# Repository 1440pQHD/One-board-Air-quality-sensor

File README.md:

# BreatheEasy - One-board-Air-quality-sensor
A simple, cheap-to-build PCB that actively monitors air quality and prevents invisible hazards. It makes protection from environmental hazards accessible to everyone.

The brains of the project are the ESP32 C3-Wroom-02

<b> Why did I choose this board? </b>

Because it includes: Wifi, Bluetooth, more than enough GPIO to last me days, and most importantly,
It's dirt cheap

List of sensors used:
BME280 (Temp & Humidity)
<br> MQ-135 (Hazardous Gas)

<p>
  Powering everything is as simple as plugging in a USB-C cable, something we should all have by now.
</p>
<p>
  The information can be read from a website that the microcontroller hosts on the local network that it's connected to.
</p>

The complete parts list includes:
1. ESP32 C3 Wroom O2
2. MQ-135 GAS sensor (Specifically the one with the digital out pin)
3. BMP280 (We love Bosh)
4. 1x 20k Ohm resistors
5. 3x 10K Ohm resistors
6. 1x 5.1KOhm resistor
7. Sparkfun USB-C Breakout module (6-pin)
8. 2x 6mm Push buttons
9. LD1117
    
The total parts list comes to about 15 euros, which is fairly cheap.
Right now, only the hardware side has been really figured out; the software side is still in early development.

The final PCB design has already been made available for anyone who wants to take a look and/or assemble the PCB.

<h1> The second iteration of the website has been released!</h1>

The second iteration of the website includes:
1. The current humidity.
2. The current temperature.
3. The current alcohol levels (this prototype uses an MQ-3 instead of an MQ-135)
4. The latest event (High temperature, Low temperature, high alcohol, etc.)
5. Uptime and time since last update.
6. An alarm played through the browser.
7. **Sub-pages for every single metric.**
8. **Live gradient for the background.**
9. **System statistics including: Available RAM and WIFI signal strength**
10. **Min/Max Values for every sensor**

<h2> How does it work? </h2>

The ESP32 reads the MQ-135 and DHT11 values through a voltage divider, since the sensor outputs up to 5v but the ESP32 can handle only 3.3V, and sends them in a JSON string to the browser you're viewing the website from.

The neat part is that, since the browser does all the heavy lifting, the ESP32 doesn't use much computing power.

The entire website structure is uploaded via a plugin called "LittleFS". It gives the ability to upload multiple files to the ESP32 to achieve an organized file structure, instead of having everything in one HTML file.

The website's modern look is achieved through fairly simple CSS.

<h2> I'm hoping by the end of the week I'll have gotten all the parts to build the final device. </h2>

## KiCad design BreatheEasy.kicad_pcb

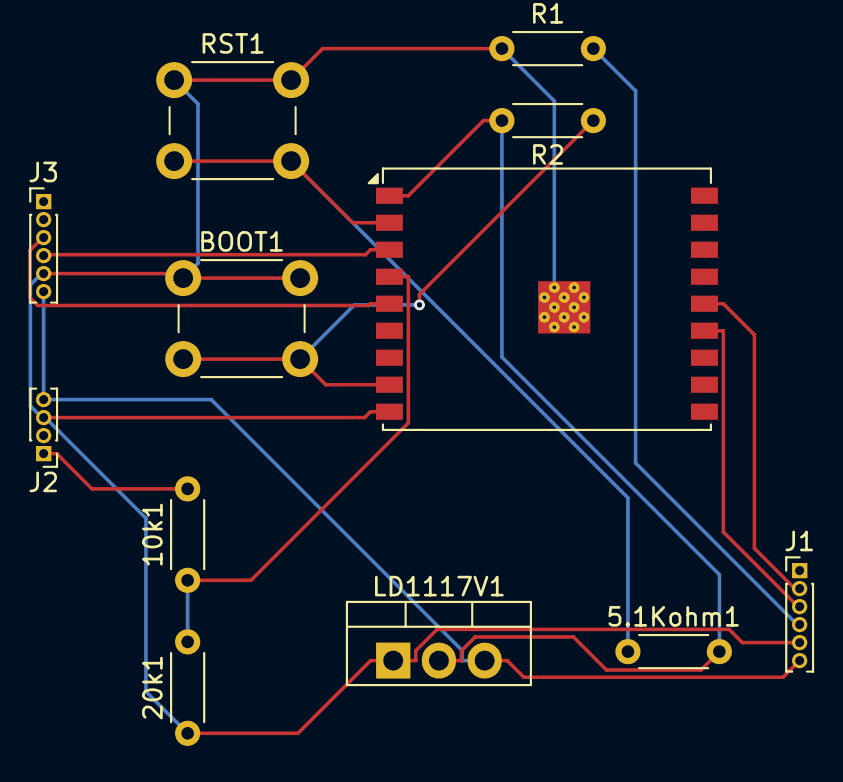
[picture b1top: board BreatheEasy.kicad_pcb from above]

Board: 2 copper layers, 12 parts (0 on the bottom side), 12 nets.

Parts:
5.1Kohm1, 10k1, 20k1: R; R_Axial_DIN0204_L3.6mm_D1.6mm_P5.08mm_Horizontal
BOOT1: SW_Push; SW_PUSH_6mm
J1: Conn_01x06_Socket; PinHeader_1x06_P1.00mm_Vertical
J2: Conn_01x04_Socket; PinHeader_1x04_P1.00mm_Vertical
J3: BMP280; PinHeader_1x06_P1.00mm_Vertical
LD1117V1: LD1117V; TO-220-3_Vertical
R1, R2: R; R_Axial_DIN0204_L3.6mm_D1.6mm_P5.08mm_Horizontal
RST1: SW_Push; SW_PUSH_6mm
U1: ESP32-C3-WROOM-02U

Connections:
unnamed: J1.2, U1.14 (IO19)
unnamed: J1.3, U1.13 (IO18)
unnamed: J1.4, R1.2
unnamed: 20k1.1, BOOT1.1, J1.5, J2.3, J3.5, LD1117V1.1 (GND), R1.1, RST1.1, U1.9 (GND), U1.19 (GND)
unnamed: J1.6, J2.4, J3.6, LD1117V1.3 (VI)
unnamed: 10k1.2, J2.1
unnamed: J3.3, U1.5 (IO6)
unnamed: J3.4, U1.3 (IO4)
unnamed: 5.1Kohm1.2, LD1117V1.2 (VO), R2.2, U1.1 (3V3)
unnamed: 5.1Kohm1.1, RST1.2, U1.2 (EN)
unnamed: 10k1.1, 20k1.2, U1.4 (IO5)
unnamed: BOOT1.2, R2.1, U1.8 (IO9)
